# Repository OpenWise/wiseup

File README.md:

WiseUp
======

Wiseup is an intelligent home assistant open source framework that consists of three basic devices Gateway, Mediators and Sensors.

##Gateway
  Based on Raspberry Pi (Galileo/Edison in the future). All data is saved in this gateway that backs up the data on Cloud      service.
  All the important analytic scripts are running locally on the Gateway and analyzing sensor data every 3 seconds.
  
  Important modules
  - Wiseup service - this layer communicates with the sensors using Wiseup protocol.
  - Node.js services - this layer contains Web Service, connection to Mongo DB (local DB) and connection to Redis Service.
  - Redis service - Publish and Subscribe feature, also for fast data storage.
  - Mongo DB - local database.
  - Analytic services - based on node.js, executes analysis script on DB for detecting sensors features.
  - And more ...

##Mediator
  Main work frequency is 2.4Ghz with private protocol, but what if we want to use other sensors from EBay or other brands?
  For that we have the mediators that will convert from our protocol and frequency to other so we'll be able to consume
  other sensors.
  
##Sensors
  We have our own sensors running on batteries or directly from 5V power.
  
##Communication 
  nRF24l01 - 2.4Ghz very low cost and low power transceiver.
  
  RFComm - Private protocol for sensors/gateway communication. 

##Developers
- Yevgeniy Kiveisha - Linux and Embedded.
- Sharon Elihis - PCB Designer and JavaScript developer.
- Aviv Ron - Architect and senior software developer.
- Yuri Shapiro - SolidWorks designer and architect.
- Jennifer Kiveisha - UI Designer and web client developer.
- Roy Beiser - Architect

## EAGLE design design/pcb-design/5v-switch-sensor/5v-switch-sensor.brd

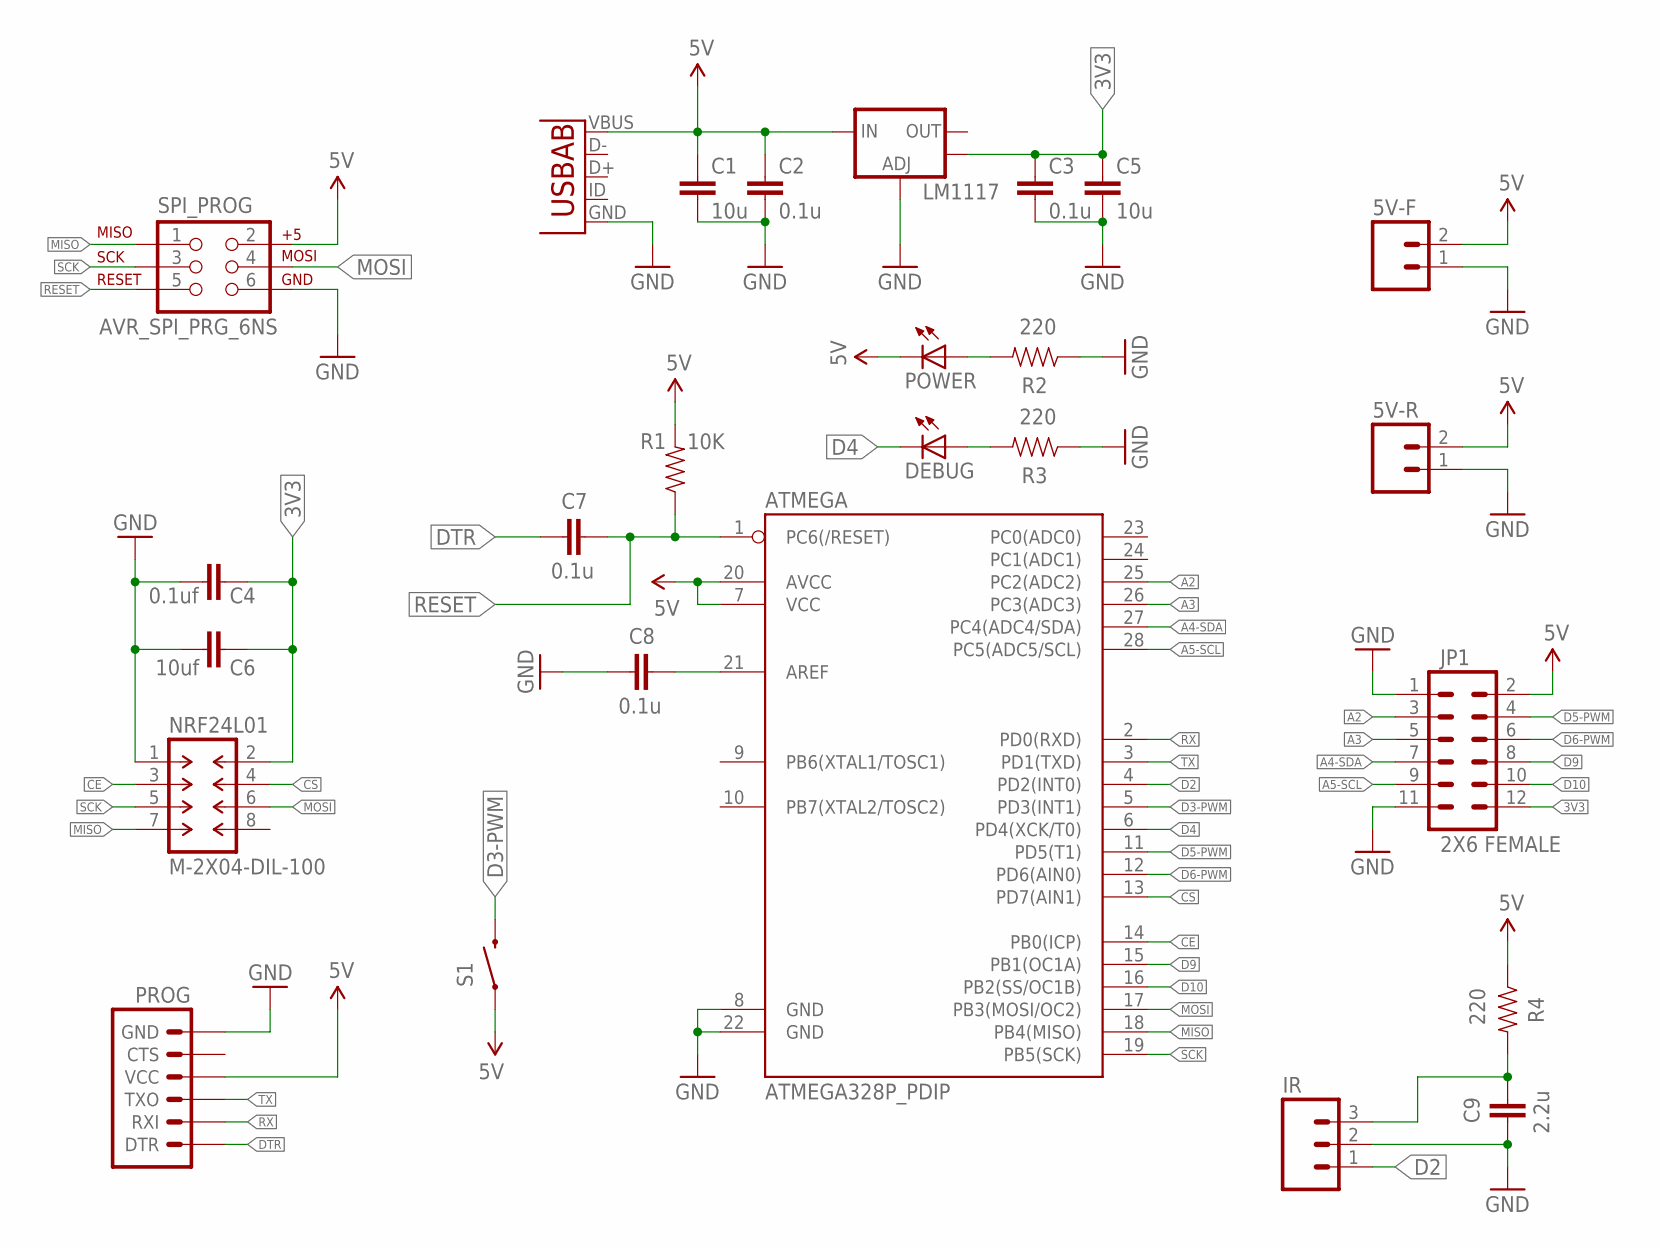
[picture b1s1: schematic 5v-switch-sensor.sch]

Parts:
5V-F, 5V-R: M02PTH; 1X02
ATMEGA: ATMEGA328P_PDIP; DIL28-3
C1, C5: 10u; 0805
C2, C3, C7, C8: 0.1u; 0805
C4: 0.1uf; 0805
C6: 10uf; 0805
C9: 2.2u; 0805
DEBUG: LEDCHIPLED_0805; CHIPLED_0805
IR: M03PTH; 1X03
JP1: 2X6 FEMALE; 2X6
LM1117: V_REG_LM1117SOT223; SOT223
NRF24L01: M-2X04-DIL-100; DIL-100-2X04
POWER: LEDCHIPLED_0805; CHIPLED_0805
PROG: ARDUINO_SERIAL_PROGRAMPTH; 1X06
R1: 10K; 0805
R2, R3, R4: 220; 0805
S1: SWITCH-MOMENTARY-2SMD-1101NE; TACTILE-SWITCH-1101NE
SPI_PROG: AVR_SPI_PRG_6NS; 2X3-NS
U1: USB-AB; USB-AB-MICRO-SMD

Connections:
3V3: C3.1, C4.1, C5.1, C6.1, JP1.12, LM1117.4 (OUT), NRF24L01.2
5V: 5V-F.2, 5V-R.2, ATMEGA.7 (VCC), ATMEGA.20 (AVCC), C1.1, C2.1, JP1.2, LM1117.3 (IN), POWER.C, PROG.4 (VCC), R1.2, R4.1, S1.1, SPI_PROG.2, U1.VBUS
A2: ATMEGA.25 (PC2(ADC2)), JP1.3
A3: ATMEGA.26 (PC3(ADC3)), JP1.5
A4-SDA: ATMEGA.27 (PC4(ADC4/SDA)), JP1.7
A5-SCL: ATMEGA.28 (PC5(ADC5/SCL)), JP1.9
CE: ATMEGA.14 (PB0(ICP)), NRF24L01.3
CS: ATMEGA.13 (PD7(AIN1)), NRF24L01.4
D2: ATMEGA.4 (PD2(INT0)), IR.1
D3-PWM: ATMEGA.5 (PD3(INT1)), S1.2
D4: ATMEGA.6 (PD4(XCK/T0)), DEBUG.C
D5-PWM: ATMEGA.11 (PD5(T1)), JP1.4
D6-PWM: ATMEGA.12 (PD6(AIN0)), JP1.6
D9: ATMEGA.15 (PB1(OC1A)), JP1.8
D10: ATMEGA.16 (PB2(SS/OC1B)), JP1.10
DTR: C7.1, PROG.1 (DTR)
GND: 5V-F.1, 5V-R.1, ATMEGA.8 (GND), ATMEGA.22 (GND), C1.2, C2.2, C3.2, C4.2, C5.2, C6.2, C8.1, C9.1, IR.2, JP1.1, JP1.11, LM1117.1 (ADJ), NRF24L01.1, PROG.6 (GND), R2.1, R3.1, SPI_PROG.6, U1.GND
MISO: ATMEGA.18 (PB4(MISO)), NRF24L01.7, SPI_PROG.1
MOSI: ATMEGA.17 (PB3(MOSI/OC2)), NRF24L01.6, SPI_PROG.4
unnamed: C9.2, IR.3, R4.2
unnamed: POWER.A, R2.2
unnamed: ATMEGA.21 (AREF), C8.2
unnamed: DEBUG.A, R3.2
RESET: ATMEGA.1 (PC6(/RESET)), C7.2, R1.1, SPI_PROG.5
RX: ATMEGA.2 (PD0(RXD)), PROG.2 (RXI)
SCK: ATMEGA.19 (PB5(SCK)), NRF24L01.5, SPI_PROG.3
TX: ATMEGA.3 (PD1(TXD)), PROG.3 (TXO)

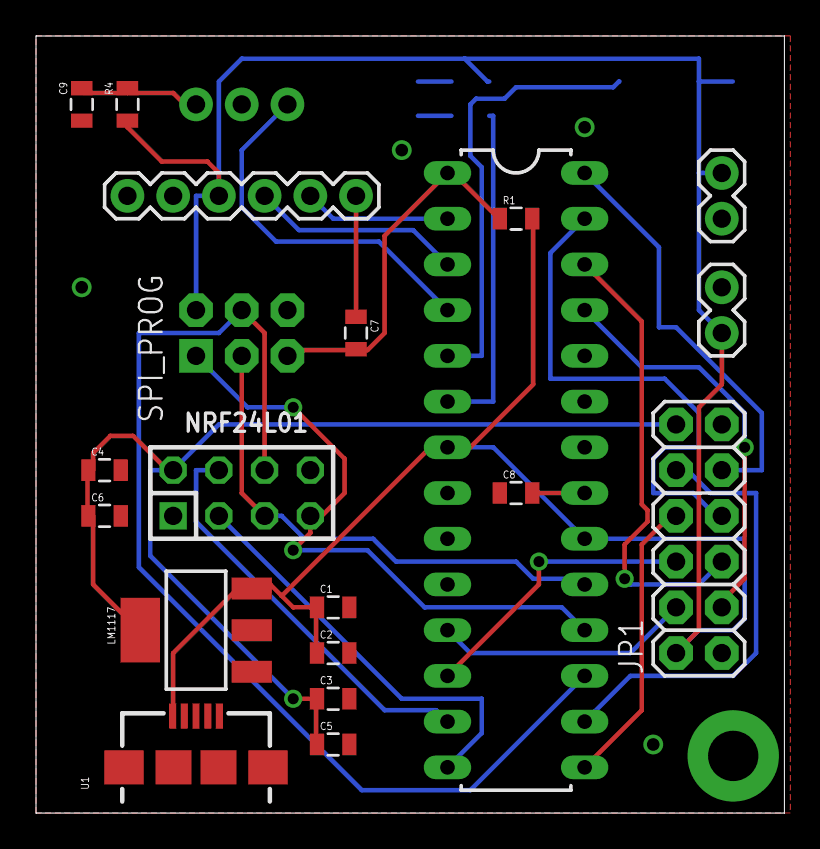
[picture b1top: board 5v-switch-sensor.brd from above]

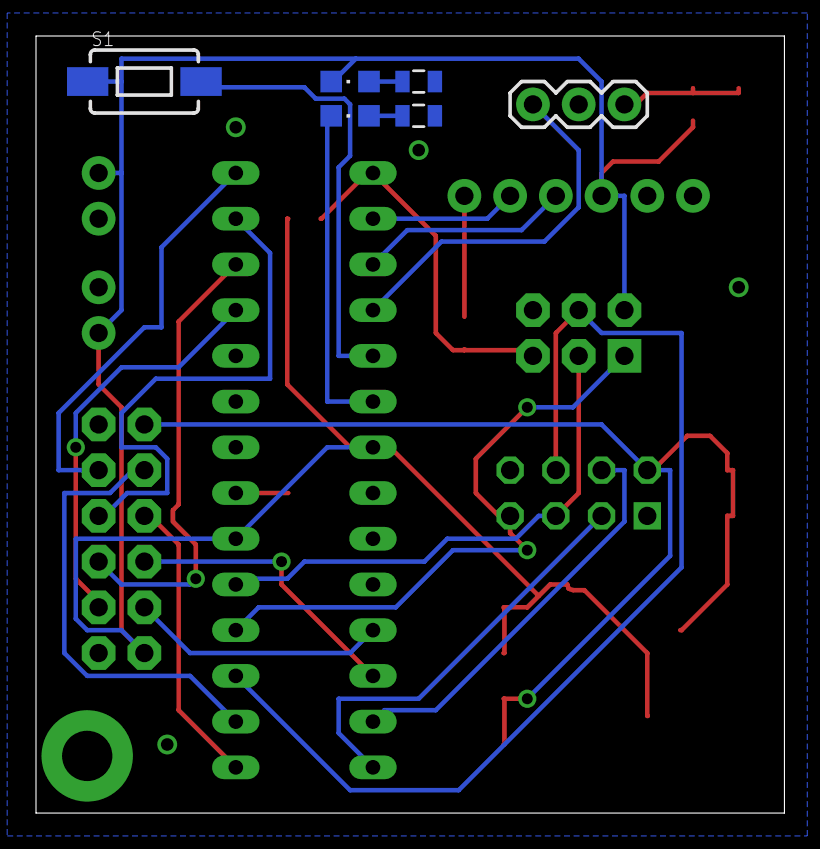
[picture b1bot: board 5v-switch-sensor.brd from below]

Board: 2 copper layers, 41.6 x 43.2 mm, 26 parts (6 on the bottom side), 27 nets.

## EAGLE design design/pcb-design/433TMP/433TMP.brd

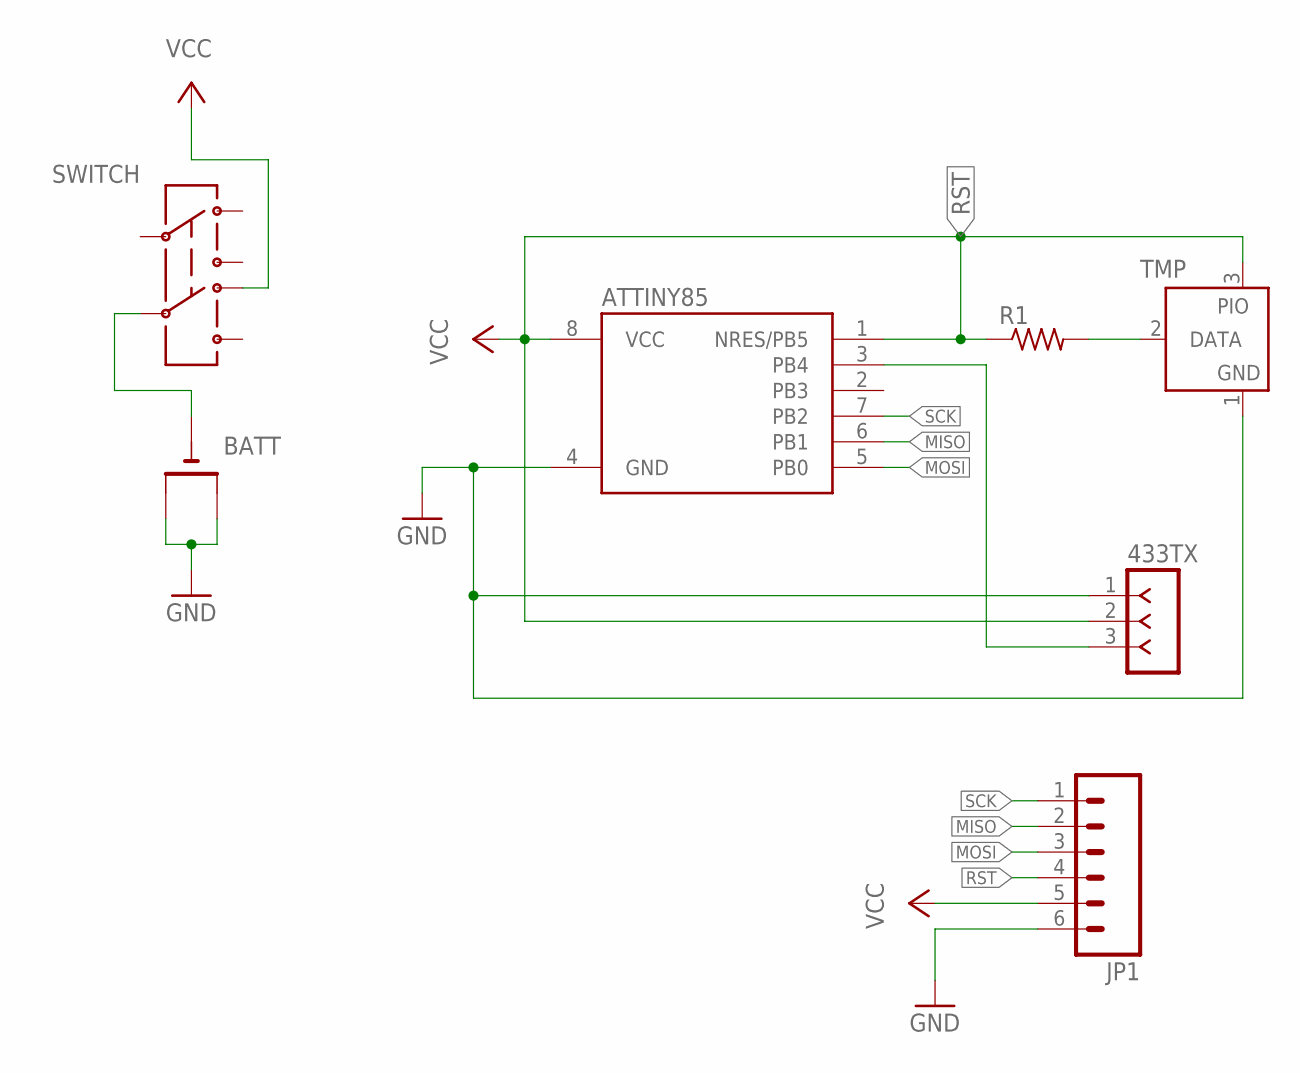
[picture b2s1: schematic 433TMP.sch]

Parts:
433TX: F-1X03-SIP-100-40; SIP-100-03-40
ATTINY85: ATTINY85-S; SOIC8_EIAJ_208MIL
BATT: CR2032SMT; CR2032-SMD
JP1: M06SILK_FEMALE_PTH; 1X06
R1: R-US_R0805; R0805
SWITCH: AYZ0202
TMP: DS2405; TO92-

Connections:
GND: 433TX.1, ATTINY85.4 (GND), BATT.+$1 (+), BATT.+$2 (+1), JP1.6, TMP.1 (GND)
MISO: ATTINY85.6 (PB1), JP1.2
MOSI: ATTINY85.5 (PB0), JP1.3
unnamed: 433TX.3, ATTINY85.3 (PB4)
unnamed: R1.2, TMP.2 (DATA)
unnamed: BATT.-, SWITCH.5
RST: 433TX.2, ATTINY85.1 (NRES/PB5), ATTINY85.8 (VCC), JP1.4, JP1.5, R1.1, SWITCH.6 (4), TMP.3 (PIO)
SCK: ATTINY85.7 (PB2), JP1.1

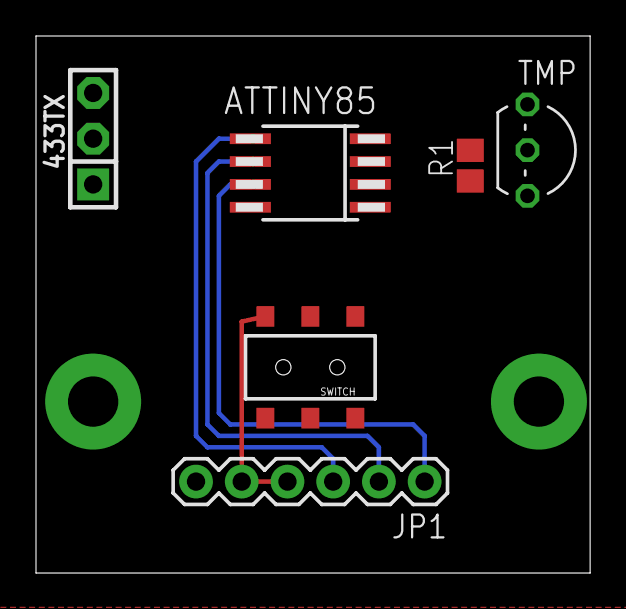
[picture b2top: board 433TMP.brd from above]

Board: 2 copper layers, 30.8 x 29.8 mm, 7 parts (1 on the bottom side), 8 nets.

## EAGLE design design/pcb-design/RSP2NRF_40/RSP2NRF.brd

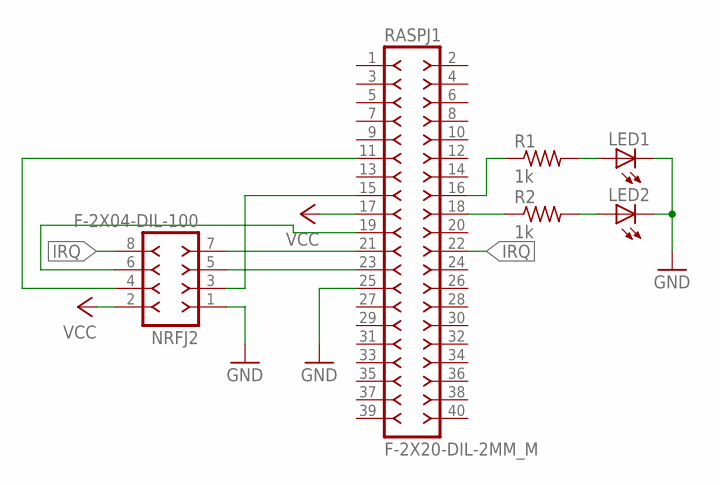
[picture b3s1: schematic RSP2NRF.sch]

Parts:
LED1, LED2: LEDCHIPLED_0805; CHIPLED_0805; MPN OVS-0808
NRFJ2: F-2X04-DIL-100; DIL-100-2X04
R1, R2: 1k; R0805; MPN CRCW20101K00FKEF
RASPJ1: F-2X20-DIL-2MM_M; DIL-2MM-2X20_M

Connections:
GND: LED1.C, LED2.C, NRFJ2.1, RASPJ1.25
IRQ: NRFJ2.8, RASPJ1.22
unnamed: NRFJ2.5, RASPJ1.23
unnamed: NRFJ2.7, RASPJ1.21
unnamed: NRFJ2.6, RASPJ1.19
unnamed: R2.1, RASPJ1.18
unnamed: NRFJ2.4, RASPJ1.11
unnamed: NRFJ2.3, RASPJ1.15
unnamed: LED2.A, R2.2
unnamed: R1.1, RASPJ1.16
unnamed: LED1.A, R1.2
S$2: RASPJ1.13
VCC: NRFJ2.2, RASPJ1.17

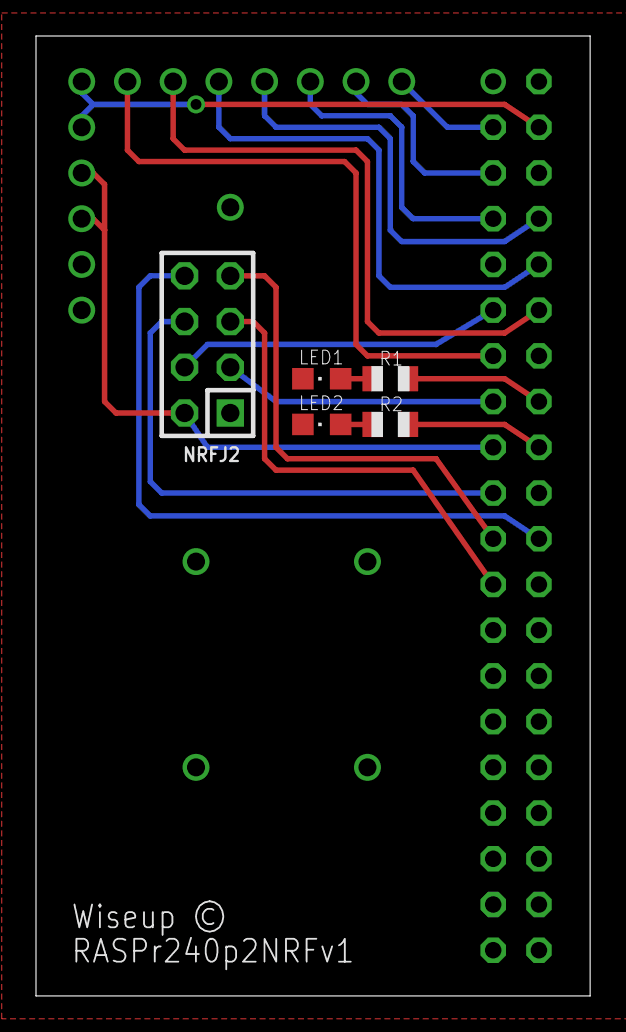
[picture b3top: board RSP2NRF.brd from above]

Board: 2 copper layers, 30.8 x 53.3 mm, 6 parts (1 on the bottom side), 12 nets.

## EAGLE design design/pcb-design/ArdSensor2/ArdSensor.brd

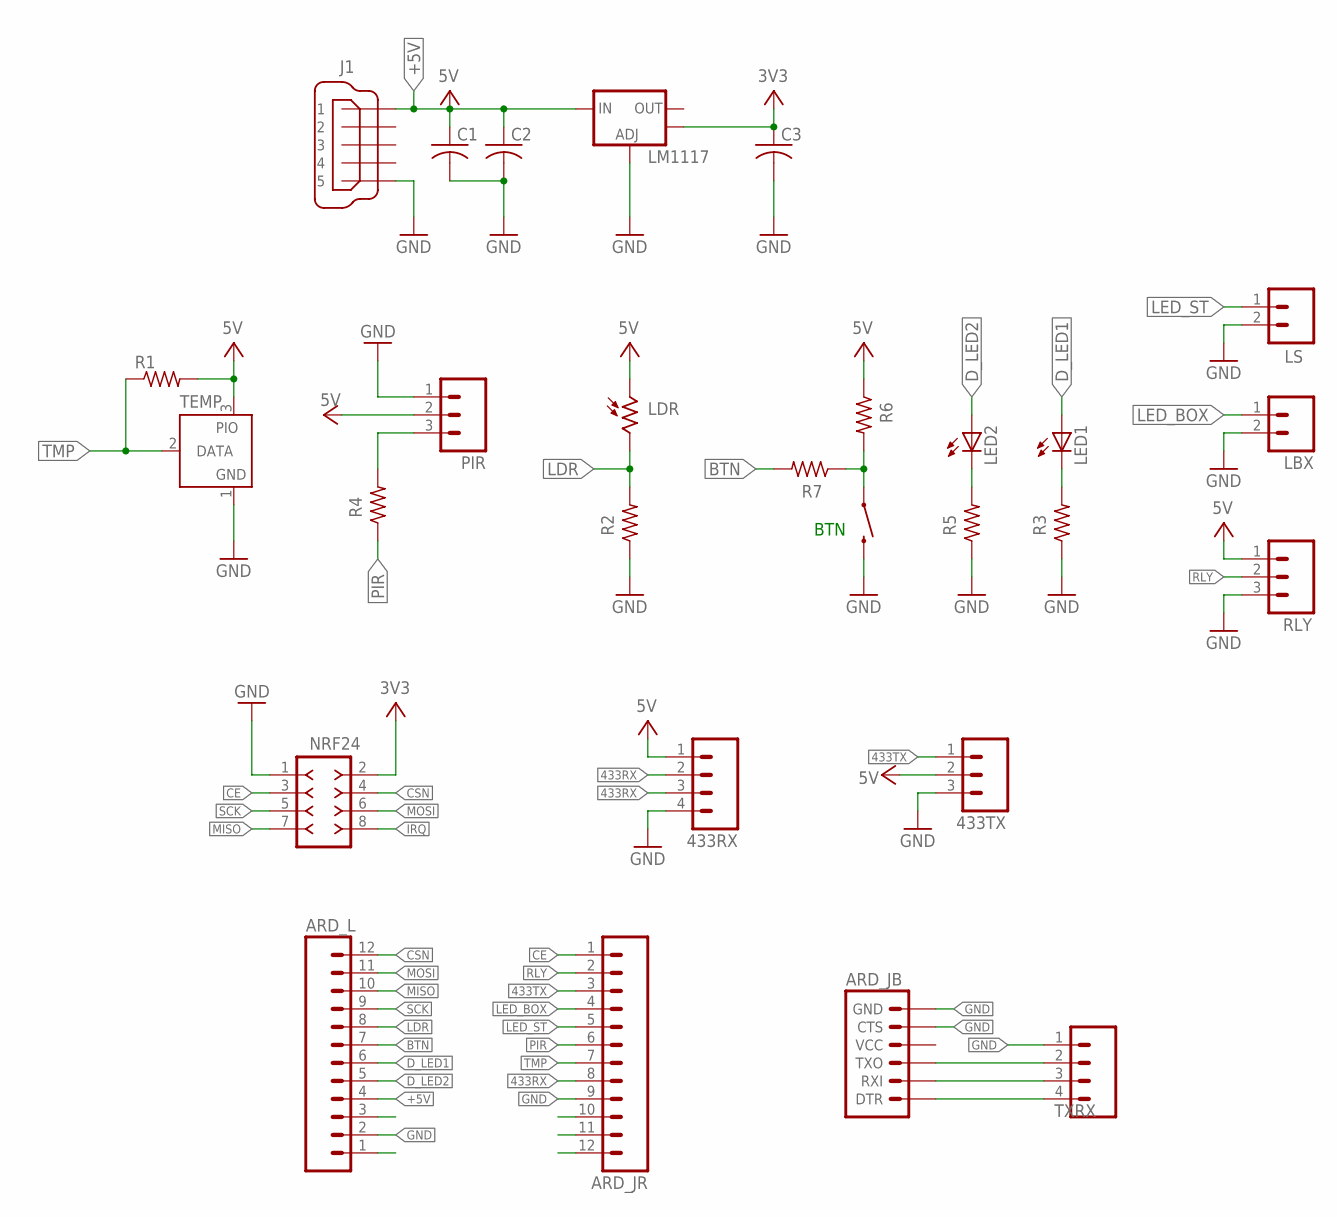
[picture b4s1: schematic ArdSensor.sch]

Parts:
433RX: M04PTH; 1X04
433TX: M03PTH; 1X03
ARD_JB: ARDUINO_SERIAL_PROGRAMPTH; 1X06
ARD_JR: M12PTH; 1X12
ARD_L: M12PTH; 1X12
BTN: SWITCH-MOMENTARY-2SMD-1101NE; TACTILE-SWITCH-1101NE
C1, C2, C3: C-USC0805; C0805
J1: MICRO-USB-ZX62R-B-5P; ZX62R-B-5P
LBX: M02PTH; 1X02
LDR: D11; BPX65
LED1, LED2: LEDCHIPLED_0805; CHIPLED_0805
LM1117: V_REG_LM1117SOT223; SOT223
LS: M02PTH; 1X02
NRF24: F-2X04-DIL-100; DIL-100-2X04
PIR: M03PTH; 1X03
R1, R2, R3, R4, R5, R6, R7: R-US_R0805; R0805
RLY: M03PTH; 1X03
TEMP: DS2405; TO92-
TXRX: M04PTH; 1X04

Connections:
433RX: 433RX.2, 433RX.3, ARD_JR.8
433TX: 433TX.1, ARD_JR.3
+3V3: C3.1, LM1117.4 (OUT), NRF24.2
+5V: 433RX.1, 433TX.2, ARD_L.4, C1.1, C2.1, J1.1, LDR.A (1), LM1117.3 (IN), PIR.2, R1.2, R6.1, RLY.1, TEMP.3 (PIO)
BTN: ARD_L.7, R7.2
CE: ARD_JR.1, NRF24.3
CSN: ARD_L.12, NRF24.4
D_LED1: ARD_L.6, LED1.A
D_LED2: ARD_L.5, LED2.A
GND: 433RX.4, 433TX.3, ARD_JB.5 (CTS), ARD_JB.6 (GND), ARD_JR.9, ARD_L.2, BTN.2, C1.2, C2.2, C3.2, J1.5, LBX.2, LM1117.1 (ADJ), LS.2, NRF24.1, PIR.1, R2.1, R3.1, R5.1, RLY.3, TEMP.1 (GND), TXRX.1
IRQ: NRF24.8
LDR: ARD_L.8, LDR.K (2), R2.2
LED_BOX: ARD_JR.4, LBX.1
LED_ST: ARD_JR.5, LS.1
MISO: ARD_L.10, NRF24.7
MOSI: ARD_L.11, NRF24.6
unnamed: LED2.C, R5.2
unnamed: LED1.C, R3.2
unnamed: PIR.3, R4.2
unnamed: BTN.1, R6.2, R7.1
unnamed: ARD_JB.3 (TXO), TXRX.2
unnamed: ARD_JB.2 (RXI), TXRX.3
unnamed: ARD_JB.1 (DTR), TXRX.4
PIR: ARD_JR.6, R4.1
RLY: ARD_JR.2, RLY.2
SCK: ARD_L.9, NRF24.5
TMP: ARD_JR.7, R1.1, TEMP.2 (DATA)

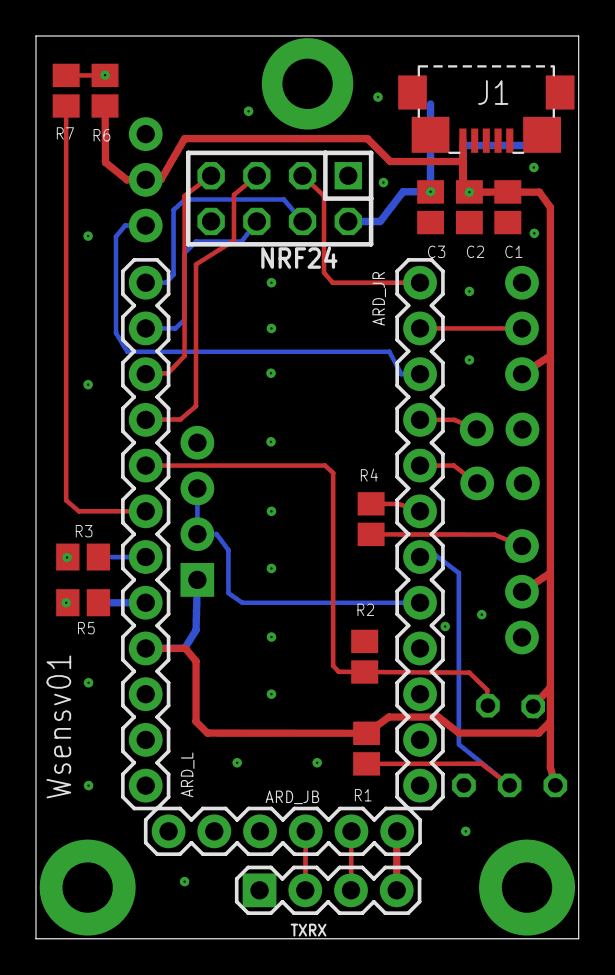
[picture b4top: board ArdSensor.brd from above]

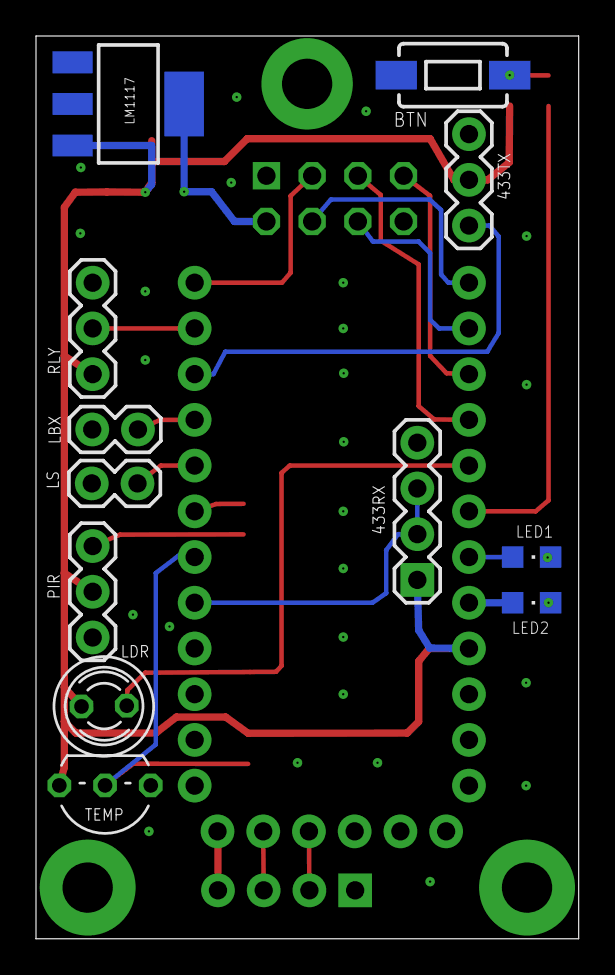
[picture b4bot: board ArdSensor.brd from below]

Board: 2 copper layers, 30.1 x 50.2 mm, 28 parts (12 on the bottom side), 26 nets.

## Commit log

2014-10-21 first commit - working environment
2014-10-24 linux: added ack management for resending requests to client
    added couple defines
2014-10-24 embedded: added ack management for requests to clients
2014-10-25 linux: added sensors availability
2014-10-25 php: added sensors availability
2014-10-25 db: added sensors availability
2014-10-29 linux: fix for ACK queue
2014-10-31 linux: simple changes to mysql class
    added wiseCacheDB class with lot of code
2014-10-31 linux: removed completely wise-dbd
    added new wise-eventd deamon (event engine)
    and more other
2014-11-01 linux: fix for unchanged cache db item by reference
2014-11-01 embedded: sensors send data only on change added keep alive option
2014-11-01 docs: added new document for pcbs and enclosures future designs
2014-11-01 linux: added KEEPALIVE support
2014-11-07 linux: removed ACK option
    removed DB deamon
    and more ...
2014-11-07 deleted files
2014-11-07 added files
2014-11-07 embedded: deleted files
2014-11-07 embedded: added used files
2014-11-07 db: update SPs
2014-11-07 php: added resend command from javascript
2014-11-08 linux: added chached sensor database to client handler module
    and more ...
2014-11-14 linux: added 433mhz wiseup (built by Omer) sensors support
2014-11-14 embedded: added new sensor hub and sensor
2014-11-23 linux: added new pcd8544 module (nokia lcd)
2014-11-26 linux: lcd working with nrf
2014-11-26 linux: db updated only on sensor data change
2014-11-26 php: sensor spred all over the dashboard
2014-11-26 linux: timer fix
2014-11-29 linux & php: robustness fix #1
2014-11-30 linux: resend action task engine is working
2014-11-30 git: added to .gitignore build folder
2014-11-30 embedded: focus on one sensor hub (motion temperature luminance and led) added feature - each sensor send its update interval to the gateway
2014-11-30 db: add/edit stored procedure
2014-11-30 repository: drivers for unknown usb to uart chip on chip nano arduino board
2014-12-01 linux & php: added connection from php to the deamon based on unix domain sockets
2014-12-02 linux: start of app framework
2014-12-05 linux added appication executors class
2014-12-05 db&embedded: new DB for the application support
2014-12-05 embedded: for got to upload dependencies
2014-12-06 Design: Added Enclosure Design for Raspberry Pi B+
2014-12-24 initial commit by aviv - added cordova app and node JS backend for REST API and SSE
2014-12-27 Added thread safe access to nrf24l01
    Added sleep for 10 micro sec to spi_write method (magically it fixed a major bug)
    Added hiredis libaray
    removed lot of code
2014-12-27 Added node.js example communication with Sensors FW via redis PUBSUB
2015-01-06 PCB design : initial checkin
2015-01-06 first working draft - connected to redis and mongodb with an API that exposes SSE and /api/sensors
2015-01-06 docs: initial NRF on battery document
2015-01-07 added ignore to node_modules for nodejs dependencies and also added sublime text editor files
2015-01-07 remove the now ignore node_modules dir
2015-01-07 remove the now ignored dir node_modules
2015-01-07 created table to see sensor values
2015-01-07 changed ip to the yevgenis raspi
2015-01-12 Linux & Node.js: Added action option. (ON/OFF)
2015-01-13 docs: removed all doc files and copied to dropbox
2015-01-13 general maintain
2015-01-15 pcb design: sensor hub update
2015-01-23 db: added new node.js file to create wiseupdb
2015-01-24 node.js: added sqlite adapter and connected the redis to sqlite
2015-01-24 node.js: ported the getAllSensors api method to sqlite
2015-01-26 node.js: fix for initial sensor info database write
2015-01-26 node.js: fix initial SSE data write
2015-01-26 node.js: test framework adopt the changes
2015-01-28 linux: added anonimus sensor info SENSOR_INFO_DATA_NO_AUTH_TYPE
2015-01-28 embedded: added anonymous sensor example
2015-02-01 added src/cordova/platforms to gitignore
2015-02-01 added cordova general ignore stuff to gitignore
2015-02-01 trying to add cordova folders to gitignore
2015-02-01 general layout + menu navigation + sensors ui
2015-02-01 formatted the document and added some comments + fix for sensor action bug
2015-02-01 fixed untracked files
2015-02-04 pcb-design: added new schematics for 5v switch/sensor base
2015-02-06 pcb-design: new board file for 5v-switch-sensor and fixes for sch file.
2015-02-06 pcb-design: [5v-switch-sensor] added noise reduction to IR circuit
2015-02-07 pcb-design: 5v pcb fixes before sendinf to imall and start of 3v pcb
2015-02-12 node.js: added onclick event and ajax request with action request (on/off)
2015-02-14 cordova-app: added new switch module (initial work)
2015-02-14 embedded: added new luminance (ldr) sensor and changed little bit led_hub
2015-02-16 cordova-app: added html removal by sensor type
2015-02-16 cordova-app: added initial values bind
2015-02-17 cordova-app: UI
2015-02-19 refactored sensors directive
2015-02-20 cordova-app: ui changes
2015-02-21 misc: before fab28 presentation
2015-02-21 cordova-app: more changes for fab28 presentation
2015-02-21 embedded: changes for fab28 presentation
2015-02-21 cordova-app: small changes to css
2015-02-28 embedded: added delay (1000) on mode change. Bug fix to issue with aa aa aa .... on gateway.

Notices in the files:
parts and their libraries:
con-headers-jp: Copyright (C) 2008, Bob Starr
sparkFun-Electromechanical: Licensing: Creative Commons ShareAlike 4.0 International - https://creativecommons.org/licenses/by-sa/4.0
